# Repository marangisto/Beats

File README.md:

# Beats
Programmable Clock Sequencer

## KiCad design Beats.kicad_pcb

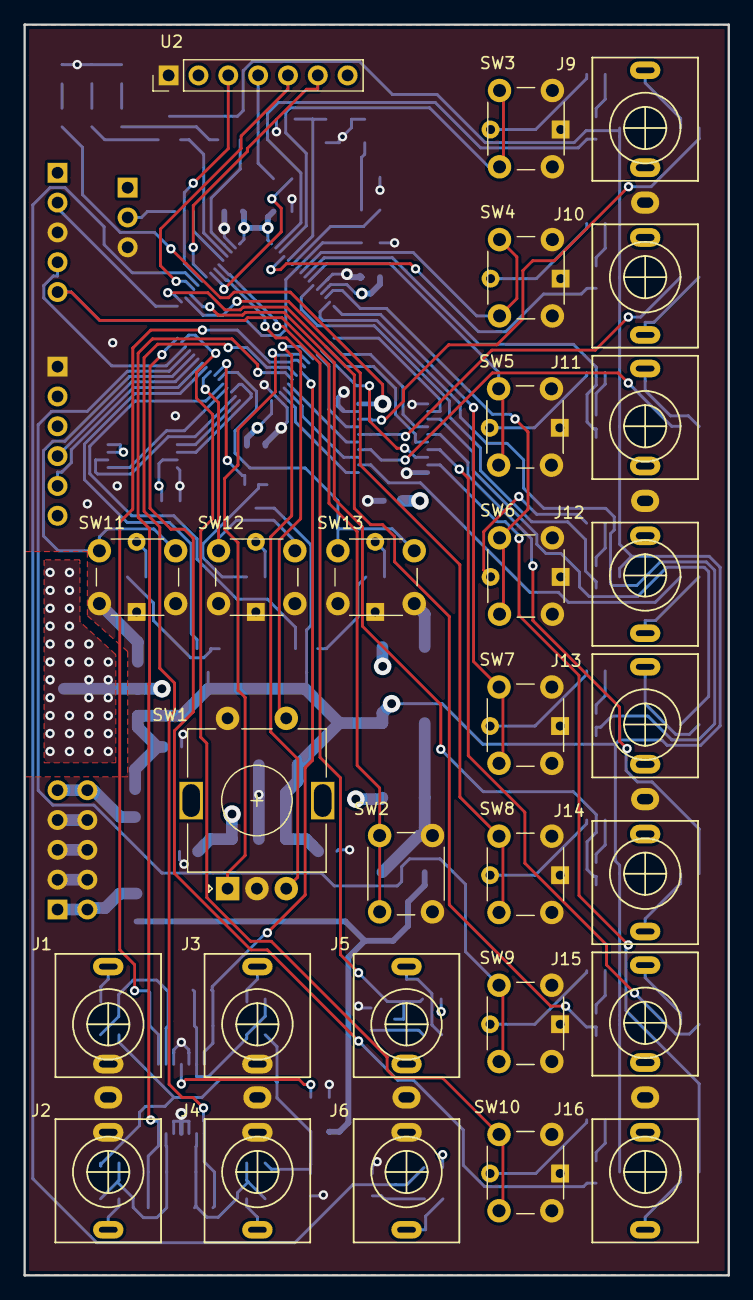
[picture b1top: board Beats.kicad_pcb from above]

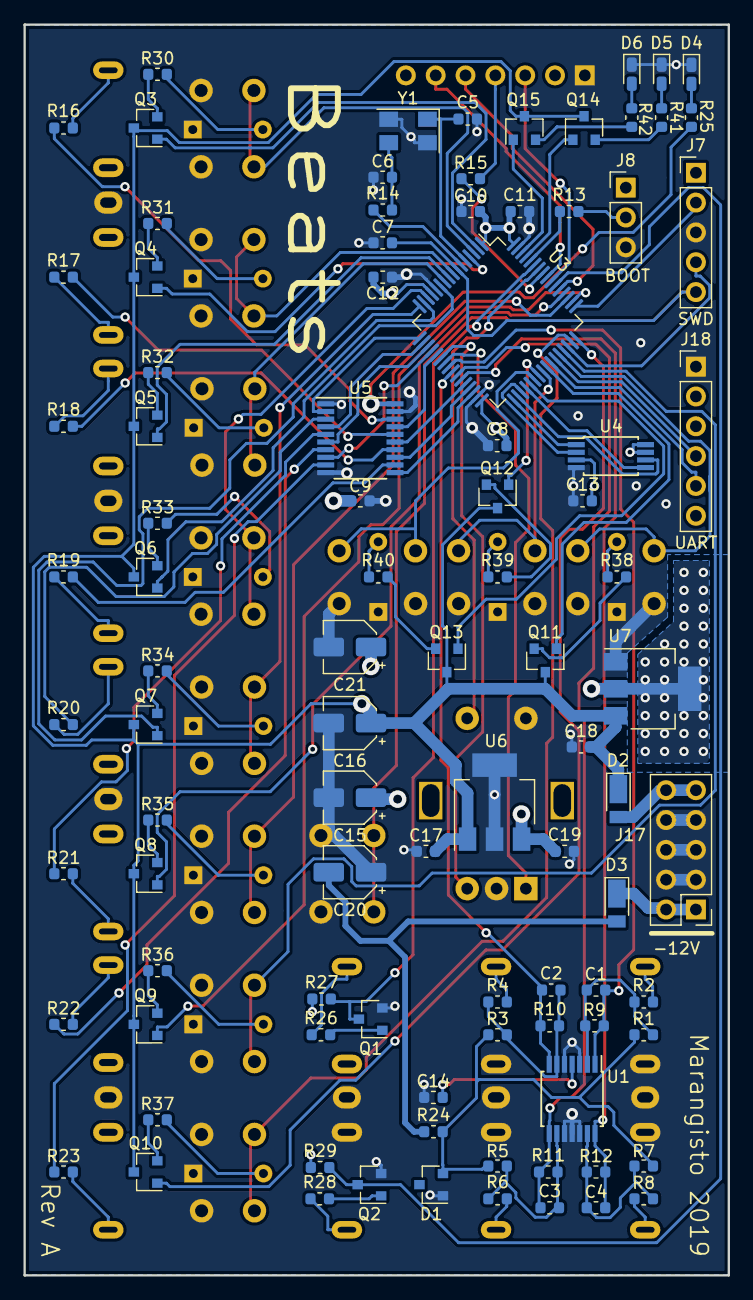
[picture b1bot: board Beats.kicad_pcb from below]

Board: 4 copper layers, 60.0 x 106.5 mm, 123 parts (95 on the bottom side), 123 nets.

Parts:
C1, C2, C3, C4: 470p; C_0603_1608Metric
C5, C6: 27p; C_0603_1608Metric
C7, C9, C10, C11, C12, C13, C14, C17, C18, C19: 100n; C_0603_1608Metric
C8: 10n; C_0603_1608Metric
C15, C16, C20, C21: 10u; CP_Elec_4x5.8
D1: LM4040DBZ-10; SOT-23
D2, D3: DFLR1400-7; D_PowerDI-123
D4, D5, D6: LED; LED_0603_1608Metric_Castellated
J1, J2, J3, J4, J5, J6, J9, J10, J11, J12, J13, J14, J15, J16: AudioJack2_SwitchT; PJ398SM
J7: SWD; PinHeader_1x05_P2.54mm_Vertical
J8: Conn_01x03_Male; PinHeader_1x03_P2.54mm_Vertical
J17: Conn_02x05_Odd_Even; PinHeader_2x05_P2.54mm_Vertical
J18: UART; PinHeader_1x06_P2.54mm_Vertical
Q1, Q2, Q3, Q4, Q5, Q6, Q7, Q8, Q9, Q10, Q11, Q12, Q13, Q14, Q15: BC847; SOT-23
R1, R3, R5, R7: 200k; R_0603_1608Metric
R2, R4, R6, R8, R26, R28: 100k; R_0603_1608Metric
R9, R10, R11, R12: 33k; R_0603_1608Metric
R13, R27, R29: 10k; R_0603_1608Metric
R14: 470; R_0603_1608Metric
R15, R16, R17, R18, R19, R20, R21, R22, R23: 1k; R_0603_1608Metric
R24: 2k2; R_0603_1608Metric
R25: 330; R_0603_1608Metric
R30, R31, R32, R33, R34, R35, R36, R37, R38, R39, R40, R41, R42: 47; R_0603_1608Metric
SW1: Rotary_Encoder_Switch; RotaryEncoder_Alps_EC11E-Switch_Vertical_H20mm
SW2: SW_Push; SW_PUSH_6mm
SW3, SW4, SW5, SW6, SW7, SW8, SW9, SW10, SW11, SW12, SW13: SW_Push_LED; SW_PUSH_LED_6mm
U1: MCP6004; TSSOP-14_4.4x5mm_P0.65mm
U2: IPS240x240
U3: STM32F051R8Tx; LQFP-64_10x10mm_P0.5mm
U4: AT25xxx; TSSOP-8_4.4x3mm_P0.65mm
U5: 74AHCT244; TSSOP-20_4.4x6.5mm_P0.65mm
U6: L7805; SOT-223-3_TabPin2
U7: LM1117-3.3; SOT-223-3_TabPin2
Y1: 8MHz; Crystal_SMD_5032-4Pin_5.0x3.2mm

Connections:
+3.3VA: C8.1, C10.1, C11.1, C12.1, C13.1, C14.1, C21.1, J5.TN, J7.1, J8.1, R27.1, R29.1, U1.4, U2.2, U2.7, U3.1, U3.13, U3.32, U3.64, U4.3, U4.7, U4.8, U7.2
+5V: C9.1, C15.1, C19.1, R25.1, U5.20, U6.3
+12V: C16.1, C17.1, C18.1, D2.1, Q3.3, Q4.3, Q5.3, Q6.3, Q7.3, Q8.3, Q9.3, Q10.3, Q11.3, Q12.3, Q13.3, Q14.3, Q15.3, U6.1, U7.3
-12V: C20.2, D3.2, R24.1
/DigitalIn/In: J5.T, R26.1
/sheet5D7C6377/In: J6.T, R28.1
GND: C5.2, C6.2, C7.2, C8.2, C9.2, C10.2, C11.2, C12.2, C13.2, C14.2, C15.2, C16.2, C17.2, C18.2, C19.2, C20.1, C21.2, D1.1, D4.1, D5.1, D6.1, J1.TN, J2.S, J2.TN, J3.TN, J4.S, J4.TN, J6.S, J6.TN, J7.3, J8.3, J10.S, J12.S, J14.S, J16.S, J17.3, J17.4, J17.5, J17.6, J17.7, J17.8, J18.1, Q1.2, Q2.2, SW1.C, SW1.S2, SW2.1, SW3.2, SW3.4, SW4.2, SW4.4, SW5.2, SW5.4, SW6.2, SW6.4, SW7.2, SW7.4, SW8.2, SW8.4, SW9.2, SW9.4, SW10.2, SW10.4, SW11.2, SW11.4, SW12.2, SW12.4, SW13.2, SW13.4, U1.3, U1.5, U1.10, U1.11, U1.12, U2.1, U3.12, U3.31, U3.63, U4.4, U5.1, U5.10, U5.19, U6.2, U7.1, Y1.2, Y1.4
unnamed: C1.2, R1.1, R2.1, R9.2, U1.2
unnamed: C2.2, R3.1, R4.1, R10.2, U1.6
unnamed: C3.2, R5.1, R6.1, R11.2, U1.9
unnamed: C4.2, R7.1, R8.1, R12.2, U1.13
unnamed: C5.1, U3.5, Y1.1
unnamed: C6.1, R14.2, Y1.3
unnamed: D2.2, J17.9, J17.10
unnamed: D3.1, J17.1, J17.2
unnamed: D4.2, R25.2
unnamed: D5.2, R41.1
unnamed: D6.2, R42.1
unnamed: J1.T, R2.2
unnamed: J2.T, R8.2
unnamed: J3.T, R4.2
unnamed: J4.T, R6.2
unnamed: J8.2, R13.2
unnamed: J9.T, R16.1
unnamed: J10.T, R17.1
unnamed: J11.T, R18.1
unnamed: J12.T, R19.1
unnamed: J13.T, R20.1
unnamed: J14.T, R21.1
unnamed: J15.T, R22.1
unnamed: J16.T, R23.1
unnamed: Q1.1, R26.2
unnamed: Q2.1, R28.2
unnamed: Q3.2, R30.2
unnamed: Q4.2, R31.2
unnamed: Q5.2, R32.2
unnamed: Q6.2, R33.2
unnamed: Q7.2, R34.2
unnamed: Q8.2, R35.2
unnamed: Q9.2, R36.2
unnamed: Q10.2, R37.2
unnamed: Q11.2, R38.2
unnamed: Q12.2, R39.2
unnamed: Q13.2, R40.2
unnamed: Q14.2, R41.2
unnamed: Q15.2, R42.2
unnamed: R13.1, U3.60
unnamed: R14.1, U3.6
unnamed: R15.1, U2.4
unnamed: R16.2, U5.18
unnamed: R17.2, U5.16
unnamed: R18.2, U5.14
unnamed: R19.2, U5.12
unnamed: R20.2, U5.3
unnamed: R21.2, U5.5
unnamed: R22.2, U5.7
unnamed: R23.2, U5.9
unnamed: R30.1, SW3.3
unnamed: R31.1, SW4.3
unnamed: R32.1, SW5.3
unnamed: R33.1, SW6.3
unnamed: R34.1, SW7.3
unnamed: R35.1, SW8.3
unnamed: R36.1, SW9.3
unnamed: R37.1, SW10.3
unnamed: R38.1, SW11.3
unnamed: R39.1, SW12.3
unnamed: R40.1, SW13.3
PA0: SW6.1, U3.14
PA1: Q7.1, U3.15
PA2: SW7.1, U3.16
PA3: U3.17, U5.2
PA4: U3.20, U5.8
PA5: U3.21, U5.17
PA6: SW1.B, U3.22
PA7: SW1.A, U3.23
PA8: Q11.1, U3.41
PA9: J18.5, U3.42
PA10: J18.4, U3.43
PA11: SW11.1, U3.44
PA12: SW9.1, U3.45
PA15: Q9.1, U3.50
PB0: C3.1, R11.1, U1.8, U3.26
PB1: C4.1, R12.1, U1.14, U3.27
PB2: U3.28, U5.15
PB3: U2.3, U3.55
PB4: U2.6, U3.56
PB5: R15.2, U3.57
PB6: SW1.S1, U3.58
PB7: Q1.3, R27.2, U3.59
PB8: Q14.1, U3.61
PB9: Q15.1, U3.62
PB10: U3.29, U5.13
PB11: U3.30, U5.11
PB12: U3.33, U4.1
PB13: U3.34, U4.6
PB14: U3.35, U4.2
PB15: U3.36, U4.5
PC0: SW4.1, U3.8
PC1: Q5.1, U3.9
PC2: SW5.1, U3.10
PC3: Q6.1, U3.11
PC4: C1.1, R9.1, U1.1, U3.24
PC5: C2.1, R10.1, U1.7, U3.25
PC6: Q13.1, U3.37
PC7: SW13.1, U3.38
PC8: Q12.1, U3.39
PC9: SW12.1, U3.40
PC10: SW8.1, U3.51
PC11: Q8.1, U3.52
PC12: U2.5, U3.53
PC13: Q3.1, U3.2
PC14: SW3.1, U3.3
PC15: Q4.1, U3.4
PD2: Q2.3, R29.2, U3.54
PF4: U3.18, U5.4
PF5: U3.19, U5.6
PF6: SW10.1, U3.47
PF7: Q10.1, U3.48
RESET: C7.1, J7.5, SW2.2, U3.7
SWCLK: J7.2, U3.49
SWDIO: J7.4, U3.46
VRef-10: D1.2, R1.2, R3.2, R5.2, R7.2, R24.2

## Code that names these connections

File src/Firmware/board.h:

#pragma once

#include <gpio.h>
#include <button.h>
#include <pulse.h>
#include <timer.h>
#include <adc.h>
#include <dma.h>
#include <st7789.h>
#include <fifo.h>
#include <message.h>

namespace board
{
typedef tim_t<6> aux;

typedef pulse_t<PA3>  out0;     // channel 0 out
typedef pulse_t<PF4>  out1;     // channel 1 out
typedef pulse_t<PF5>  out2;     // channel 2 out
typedef pulse_t<PA4>  out3;     // channel 3 out
typedef pulse_t<PA5>  out4;     // channel 4 out
typedef pulse_t<PB2>  out5;     // channel 5 out
typedef pulse_t<PB10> out6;     // channel 6 out
typedef pulse_t<PB11> out7;     // channel 7 out

typedef pulse_t<PC13> led0;     // channel 0 led
typedef pulse_t<PC15> led1;     // channel 1 led
typedef pulse_t<PC1>  led2;     // channel 2 led
typedef pulse_t<PC3>  led3;     // channel 3 led
typedef pulse_t<PA1>  led4;     // channel 4 led
typedef pulse_t<PC11> led5;     // channel 5 led
typedef pulse_t<PA15> led6;     // channel 6 led
typedef pulse_t<PF7>  led7;     // channel 7 led

typedef pulse_t<PA8> ledA;      // user led 8
typedef pulse_t<PC8> ledB;      // user led 9
typedef pulse_t<PC6> ledC;      // user led 10

typedef pulse_t<PB8> ledX;      // rear red led
typedef pulse_t<PB9> ledY;      // rear yellow led

typedef button_t<PC14> btn0;    // user button 0
typedef button_t<PC0>  btn1;    // user button 1
typedef button_t<PC2>  btn2;    // user button 2
typedef button_t<PA0>  btn3;    // user button 3
typedef button_t<PA2>  btn4;    // user button 4
typedef button_t<PC10> btn5;    // user button 5
typedef button_t<PA12> btn6;    // user button 6
typedef button_t<PF6>  btn7;    // user button 7

typedef button_t<PA11> btnA;    // user button 8
typedef button_t<PC9>  btnB;    // user button 9
typedef button_t<PC7>  btnC;    // user button 10
typedef button_t<PB6>  btnE;    // encoder button

typedef input_t<PB7> clk;       // clock input
typedef input_t<PD2> rst;       // reset input

typedef encoder_t<3, PA6, PA7> enc;
typedef st7789_t<1, PB3, PB5, PB4, PC12> tft;
typedef fifo_t<message_t, 0, 8> mq;

typedef adc_t<1> adc;
typedef dma_t<1> adc_dma;
typedef tim_t<15> adc_tim;

static const uint8_t adc_dma_ch = 1;
static const uint8_t adc_buf_size = 4;
static uint16_t adc_buf[adc_buf_size];
static const uint32_t adc_sample_freq = 2000;

template<uint8_t CH> inline uint16_t cvin();

template<> inline uint16_t cvin<0>() { return 4095 - adc_buf[2]; }
template<> inline uint16_t cvin<1>() { return 4095 - adc_buf[1]; }
template<> inline uint16_t cvin<2>() { return 4095 - adc_buf[3]; }
template<> inline uint16_t cvin<3>() { return 4095 - adc_buf[0]; }

void setup()
{
    out0::setup();
    out1::setup();
    out2::setup();
    out3::setup();
    out4::setup();
    out5::setup();
    out6::setup();
    out7::setup();

    led0::setup();
    led1::setup();
    led2::setup();
    led3::setup();
    led4::setup();
    led5::setup();
    led6::setup();
    led7::setup();
    ledA::setup();
    ledB::setup();
    ledC::setup();

    ledX::setup();
    ledY::setup();

    btn0::setup<pull_up>();
    btn1::setup<pull_up>();
    btn2::setup<pull_up>();
    btn3::setup<pull_up>();
    btn4::setup<pull_up>();
    btn5::setup<pull_up>();
    btn6::setup<pull_up>();
    btn7::setup<pull_up>();

    btnA::setup<pull_up>();
    btnB::setup<pull_up>();
    btnC::setup<pull_up>();
    btnE::setup<pull_up>();

    clk::setup();
    rst::setup();

    enc::setup<pull_up>(1 + (64 << 1));

    aux::setup(48-1, 1000-1); // 1kHz
    aux::enable_update_interrupt();
    interrupt::set<interrupt::TIM6_DAC>();

    adc_tim::setup(1, (sys_clock::freq() >> 1) / adc_sample_freq - 1);
    adc_tim::master_mode<adc_tim::mm_update>();
    adc_dma::setup();
    adc::setup();
    adc::sequence<8, 9, 14, 15>(); // PB0, PB1, PC4, PC5
    adc::dma<adc_dma, adc_dma_ch>(adc_buf, adc_buf_size);
    adc::trigger<0x4>(); // FIXME: use symbol for TIM15_TRIGO
    adc::enable();
    adc::start_conversion();

    tft::setup<fpclk_2>();
}

} // namespace board

template<typename BTN, typename MQ, int NO>
static void update()
{
    BTN::update();
    if (BTN::read())
    {
        MQ::put(message_t().emplace<button_press>(NO));
        board::ledX::pulse(100);
    }
}

template<> void handler<interrupt::TIM6_DAC>()
{
    using namespace board;

    aux::clear_update_interrupt_flag();

    out0::update();
    out1::update();
    out2::update();
    out3::update();
    out4::update();
    out5::update();
    out6::update();
    out7::update();

    update<btn0, mq, 0>();
    update<btn1, mq, 1>();
    update<btn2, mq, 2>();
    update<btn3, mq, 3>();
    update<btn4, mq, 4>();
    update<btn5, mq, 5>();
    update<btn6, mq, 6>();
    update<btn7, mq, 7>();

    update<btnA, mq, 10>();
    update<btnB, mq, 11>();
    update<btnC, mq, 12>();

    if (btnE::update_read())
        mq::put(message_t().emplace<encoder_press>(unit));

    static int16_t enc_last_count = 0;
    int16_t c = static_cast<int16_t>(enc::count()) >> 1;

    if (c != enc_last_count)
    {
        int16_t n = c - enc_last_count;

        // hack around weird glitch

        if (n == 64)
            n = -1;
        else if (n == -64)
            n = 1;

        mq::put(message_t().emplace<encoder_delta>(n));
        enc_last_count = c;
        ledY::pulse(25);
    }

    led0::update();
    led1::update();
    led2::update();
    led3::update();
    led4::update();
    led5::update();
    led6::update();
    led7::update();
    ledA::update();
    ledB::update();
    ledC::update();
    ledX::update();
    ledY::update();
}

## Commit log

2019-05-15 Added footprint and model for display.
2019-05-18 Added footprint and 3d model for led push button.
2019-05-18 Added mechanical rendering.
2019-05-20 First schematic (missing TFT & led-buttons).
2019-05-21 Use 74AHCT244.
2019-05-21 Added symbols and adjusted footprints.
2019-05-22 Added eeprom.
2019-05-22 Footprint for eeprom.
2019-05-23 Allocated analog inputs.
2019-05-25 Initial firmware.
2019-05-25 Double step detents.
2019-05-25 Some encoder wiring.
2019-05-25 Added footprint for jacks.
2019-05-25 Edgecuts and user drawing.
2019-05-25 Initial pin assignments and placement.
2019-05-26 Spiced the led driver to size resistor for approx 10mA.
2019-05-26 Added UART and corresponding pin assignments.
2019-05-26 Assigned trigger output pins.
2019-05-26 Corrected port collisions.
2019-05-26 Correct placement of reset switch.
2019-05-26 Assigned led and switch pins.
2019-05-26 Update pin-assignment sheet.
2019-05-26 Added board dimensions.
2019-05-26 All pins assigned and connected.
2019-05-26 Shared pads adjusment, four-layers and ground-plane fill.
2019-05-26 Improved component placement.
2019-05-26 Fixed wrong voltage on clock / reset inputs and better wiring.
2019-05-26 Power and ground planes routed and poured.
2019-05-26 Keep-outs for jacks.
2019-05-26 Front silk-screen.
2019-05-26 Back silk-screen.
2019-05-26 Branding and legends.
2019-05-26 Pin assingment for input clock and reset signals.
2019-05-26 Free-routed signals.
2019-05-27 Added board trace image.
2019-05-27 Added board renderings.
2019-05-27 Added BOM.
2019-05-27 Stitching of head-sinks for 3.3V.
2019-05-27 Revised chip power connections.
2019-05-27 Pours on top and bottom layers.
2019-05-27 Generated Gerbers.
2019-06-04 Demo implentation of Euclidean rythm algorithm in Haskell.
2019-06-04 Added alternative Haskell implementation.
2019-06-04 Clean-up of Haskell implementations.
2019-06-05 First C++ implementation of Euclidean Rythm Algorithm.
2019-06-05 Don't use multiple using.
2019-06-05 Header and conditional test complilation.
2019-06-05 Added minimal list implementation.
2019-06-05 Copy and assignment of lists.
2019-06-05 Fixed bug in list destructor.
2019-06-05 First working Euclidean on the MCU.
2019-06-05 Ignore precompiled headers.
2019-06-05 Introduced sequence class.
2019-06-05 Added cursor.
2019-06-05 Extended capability to 64-step sequences.
2019-06-05 Run two channels in parallel.
2019-06-06 Use divMod and simplify.
2019-06-06 More clean-up of Euclidean in Haskell.
2019-06-06 Updated C++ Euclidean based on Haskell prototype.
2019-06-06 Very busy 8-channel display.
2019-06-08 Added separate firmware for inital bring-up of board.
2019-06-08 All buttons and leds tested.
2019-06-08 Added outputs.
2019-06-15 Use new hal library.
2019-06-15 Updated boot program for new hal.
2019-06-19 Added display hardware mappings.
2019-06-19 Added encoder hardware mappings and show output.
2019-06-19 First working hardware version.
2019-06-19 Feed through trigger outputs.
2019-06-20 Modal control of step count.
2019-06-24 Added emulator for painless GUI dev-work.
2019-06-24 Corrections for standard RGB color scheme.
2019-06-25 Compute and apply padding for text box background.
2019-06-29 Draft GUI layout.
2019-06-29 Experimental widget.
2019-06-30 Use widget.
2019-07-01 Added emulation for actual input hardware.
2020-02-22 Fixed compilation error.
2020-02-22 Added blink example.
2020-02-22 Moved main firmware to separate subdirectory.
2020-02-22 Added basic test for screen.
2020-02-22 Restructured completely.
2020-02-22 Added version number.
2020-02-22 Use EXTI interrupts for clock and reset inputs.
2020-02-22 Corrected aux-timer to 1kHz.
2020-02-22 Added time-to-clear method to leds.
2020-02-23 Initial ADC test skeleton.
2020-02-23 Initial ADC setup.
2020-02-23 Working ADC DMA.
2020-02-23 Added templated accessors for cv-input.
2020-02-23 Moved ADC handling to board header.
2020-02-23 Common color definitons.
2020-02-23 Editable range bounded bpm.
2020-02-23 Added master bpm clock and control.
2020-02-23 Run-state control.
2020-02-23 Moved trigger handlers to clock module.
2020-02-23 Do some extra blinking on triggers.
2020-02-23 Added automatic switching between external and internal clocks.
2020-02-23 Update clock source in gui.
2020-02-23 Introduced extra clock for measuring external bpm.
2020-02-24 Added EXTI example to debug interrupt handler.
2020-02-24 Realized reset trigger is on a separate interrupt.
2020-02-24 Fixed reset interrupt problem.
2020-02-24 Measure external bpm and handle switching from internal to external.
2020-02-24 Use separate timer interrupt to monitor external clock.
2020-02-24 Removed probe in UI input polling interrupt.
2020-02-25 Moved pulse generating output to hal library.
2020-02-26 Common tick counter and use pulsed trigger outputs.
2020-02-29 Started adding channel logic.
2020-02-29 Basic Euclidean functionality.
2020-02-29 Generate output for all channels.
2020-03-01 Move sequnce generation to separate module.
2020-03-01 Started work on sequence ui.
2020-03-07 Use new widget.
2020-03-07 Started migration to new widget.
2020-03-14 Upgraded ADC test for new widget.
2020-03-14 Restructuring for better gui management.
2020-03-15 Integrate gui in sequence generator.
2020-03-15 Removed obsolete code.
2020-03-15 Share gui across channels.
2020-03-15 Added labels.
2020-03-16 Custom widgets for skew and direction.
2020-03-16 More constraints.
2020-03-17 Return to main window if same channel is reselected.
2020-03-17 Don't overrun reduced steps.
2020-03-17 Prepare for graphics.
2020-03-19 Broke graphics into separate header.
2020-03-19 Wired clock ticks through message queue.
2020-03-20 Working graphics.
2020-03-20 Added colors and use base-0 index for channel labels.
2020-03-20 Added graded background colors.
2020-03-20 Pass background color to region.
2020-03-21 Better brown.
2020-03-21 Use magic number for graphic spacing.
2020-03-21 Prettier graphics.
2020-03-21 Template gui on display.
2020-03-21 Don't abbreviate mode display.
2020-03-21 Embedded graphic in panel with spacer and later tool-bar.
2020-03-21 Clock is widget, not a window for better compositon.
2020-03-21 Added tool-bar.
2020-03-21 Color coded channel window.
2020-03-21 Keep tracks in background while editing (less disruptive ui).
2020-03-21 Implemented sequence rotation.
2020-08-16 Added test for encoder.
2020-08-16 Ported to corona.
